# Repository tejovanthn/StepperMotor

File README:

Stepper motor breakout board based on TI's DRV8824/5

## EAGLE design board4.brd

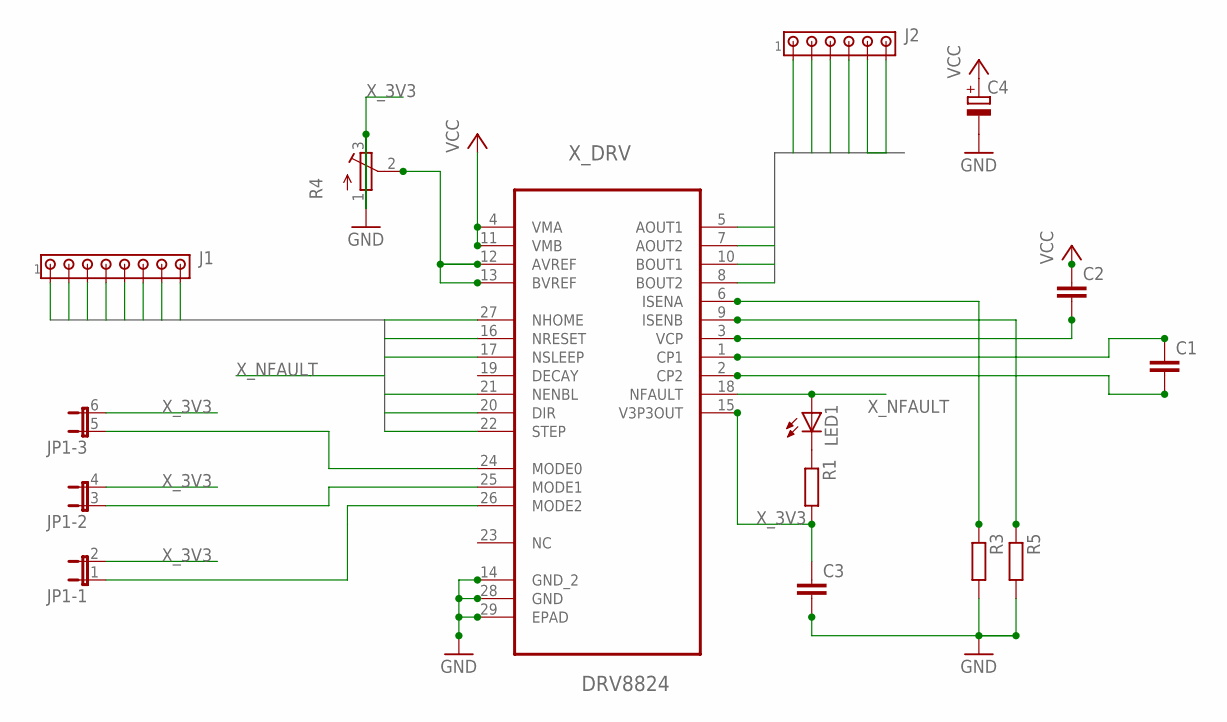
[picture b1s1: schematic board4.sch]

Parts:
C1, C2, C3: C-EUC0805; C0805
C4: CPOL-EUE5-10.5; E5-10,5
J1: MTA08-100; 10X08MTA
J2: MTA06-156; 1X6MTA
JP1: JP3QE; JP3Q
LED1: LEDCHIPLED_0805; CHIPLED_0805
R1, R3, R5: R-EU_M0805; M0805
R4: R-TRIMM4G/J; RTRIM4G/J
X_DRV: DRV8824; SOP65P640X120-29N

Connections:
GND: C3.2, C4.-, J1.8, J2.5, R3.2, R4.3 (E), R5.2, X_DRV.14 (GND_2), X_DRV.28 (GND), X_DRV.29 (EPAD)
unnamed: JP1.1, X_DRV.26 (MODE2)
unnamed: JP1.3 (1), X_DRV.25 (MODE1)
unnamed: JP1.5 (1), X_DRV.24 (MODE0)
unnamed: LED1.C, R1.1
unnamed: R4.2 (S), X_DRV.12 (AVREF), X_DRV.13 (BVREF)
unnamed: C1.1, X_DRV.1 (CP1)
unnamed: C1.2, X_DRV.2 (CP2)
unnamed: C2.2, X_DRV.3 (VCP)
unnamed: R3.1, X_DRV.6 (ISENA)
unnamed: R5.1, X_DRV.9 (ISENB)
VCC: C2.1, C4.+, J2.6, X_DRV.4 (VMA), X_DRV.11 (VMB)
XOUT0: J2.1, X_DRV.5 (AOUT1)
XOUT1: J2.2, X_DRV.7 (AOUT2)
XOUT2: J2.3, X_DRV.10 (BOUT1)
XOUT3: J2.4, X_DRV.8 (BOUT2)
X_3V3: C3.1, JP1.2, JP1.4 (2), JP1.6 (2), R1.2, R4.1 (A), X_DRV.15 (V3P3OUT)
X_DIR: J1.2, X_DRV.20 (DIR)
X_NENBL: J1.3, X_DRV.21 (NENBL)
X_NFAULT: J1.7, LED1.A, X_DRV.18 (NFAULT)
X_NHOME: J1.6, X_DRV.27 (NHOME)
X_NRESET: J1.5, X_DRV.16 (NRESET)
X_NSLEEP: J1.4, X_DRV.17 (NSLEEP)
X_STEP: J1.1, X_DRV.22 (STEP)

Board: 2 copper layers, 13 parts (5 on the bottom side), 24 nets, no tracks yet.

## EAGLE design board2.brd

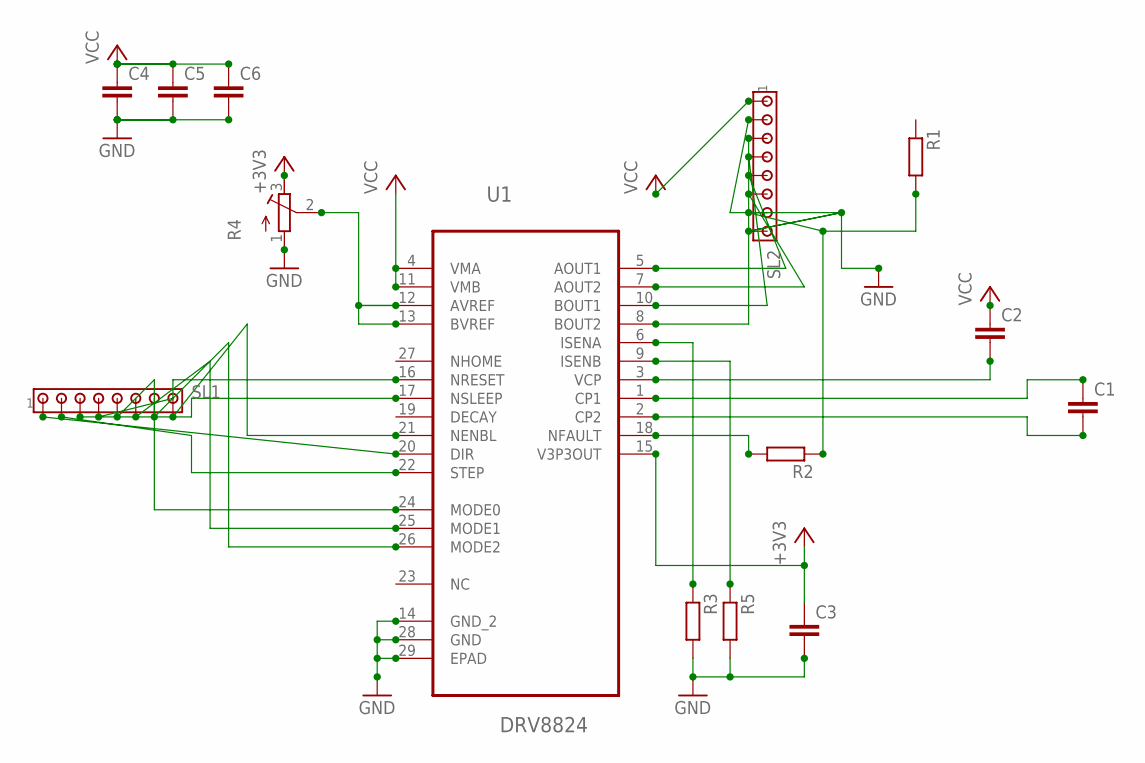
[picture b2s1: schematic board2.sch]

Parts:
C1, C2, C3, C4, C5, C6: C-EUC0805; C0805
R1, R2, R3, R5: R-EU_M0805; M0805
R4: R-TRIMM4G/J; RTRIM4G/J
SL1, SL2: MTA08-100; 10X08MTA
U1: DRV8824; SOP65P640X120-29N

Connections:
+3V3: C3.1, R4.3 (A), U1.15 (V3P3OUT)
AOUT1: SL2.5, U1.5 (AOUT1)
AOUT2: SL2.6, U1.7 (AOUT2)
BOUT1: SL2.4, U1.10 (BOUT1)
BOUT2: SL2.3, U1.8 (BOUT2)
GND: C3.2, C4.2, C5.2, C6.2, R3.2, R4.1 (E), R5.2, SL2.2, SL2.8, U1.14 (GND_2), U1.28 (GND), U1.29 (EPAD)
unnamed: SL1.1, U1.20 (DIR)
unnamed: SL1.2, U1.22 (STEP)
unnamed: SL1.3, U1.17 (NSLEEP)
unnamed: SL1.4, U1.16 (NRESET)
unnamed: SL1.5, U1.24 (MODE0)
unnamed: SL1.6, U1.25 (MODE1)
unnamed: SL1.7, U1.26 (MODE2)
unnamed: SL1.8, U1.21 (NENBL)
unnamed: R4.2 (S), U1.12 (AVREF), U1.13 (BVREF)
unnamed: C1.1, U1.1 (CP1)
unnamed: C1.2, U1.2 (CP2)
unnamed: C2.2, U1.3 (VCP)
unnamed: R2.2, U1.18 (NFAULT)
unnamed: R1.2, R2.1, SL2.7
unnamed: R3.1, U1.6 (ISENA)
unnamed: R5.1, U1.9 (ISENB)
VCC: C2.1, C4.1, C5.1, C6.1, SL2.1, U1.4 (VMA), U1.11 (VMB)

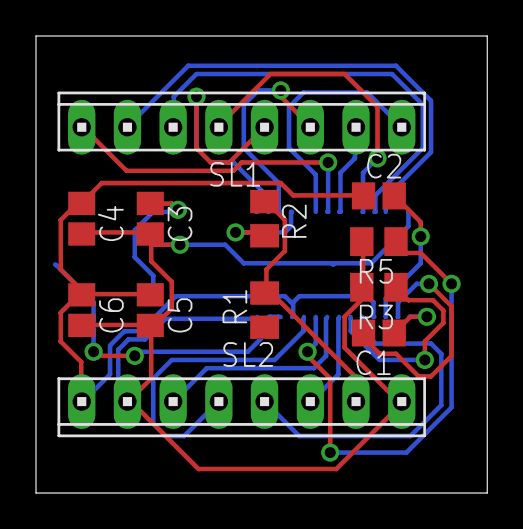
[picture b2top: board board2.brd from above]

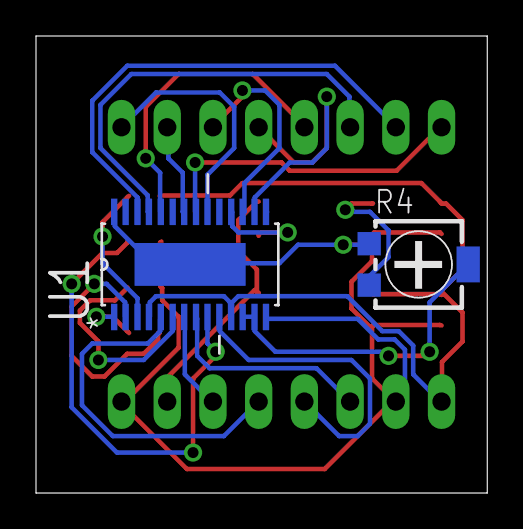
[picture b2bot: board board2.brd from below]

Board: 2 copper layers, 25.1 x 25.4 mm, 14 parts (2 on the bottom side), 23 nets.

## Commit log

2014-07-31 Initial
2014-08-09 More configurations
